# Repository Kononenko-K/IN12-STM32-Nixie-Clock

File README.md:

# IN12-STM32-Nixie-Clock

STM32 Nixie clock project with four Soviet IN-12 indicators.

<br/>

## Overview

<br/>

This project provides a complete solution for building an STM32-powered 
Nixie clock with Soviet IN-12 tubes. It operates on a 5V power supply 
via a Type-C connector and features an internal high voltage generator.

## Hardware

<br/>

### [**Display Module**](/Hardware/nixie%20display/project.pdf)
- Utilizes the K155ID1 (equivalent to SN74141N) as a high-voltage 
BCD-to-decimal decoder.
- Drives four Nixie tubes using dynamic scanning with TLP627 optocouplers.

### [**Controller Module**](/Hardware/mcu%20board/project.pdf)
- Based on the STM32F103C8Tx microcontroller, featuring:
  - Internal RTC peripheral for timekeeping;
  - Battery input for maintaining time during power off;
  - Boost converter for high-voltage generation using a PWM signal from 
one of the MCU's timers;
  - Four WS2812B addressable RGB LEDs for tube illumination.

### **Connection Guide**

| **Display Module** | **Controller Module** |
|--------------------|-----------------------|
| A1                 | PA4                   |
| A2                 | PA6                   |
| A3                 | PB0                   |
| A4                 | PB2                   |
|--------------------|-----------------------|
| D0                 | PA5                   |
| D1                 | PB1                   |
| D2                 | PB10                  |
| D3                 | PA7                   |
|--------------------|-----------------------|
| NE                 | PA10                  |
|--------------------|-----------------------|
| +180V              | HV                    |
|--------------------|-----------------------|
| +5V                | +5V                   |

Connect all respective GNDs together.

## Firmware

The firmware is developed as a Makefile project, generated with 
STM32CubeMX. It can be built using:

```sh
make clean && make
```

To upload the firmware, use ST-LINK/V2 and OpenOCD with the following 
command:

```sh
openocd -f interface/stlink.cfg \
          -f target/stm32f1x.cfg \
          -c "init; reset halt; flash write_image erase ./build/new_nixie.bin 0x08000000; reset halt; exit"
```

The code implements firmware protection and it can be removed with:
```sh
openocd -f interface/stlink.cfg \
          -f target/stm32f1x.cfg \
          -c "init; reset halt; stm32f1x unlock 0; reset halt; exit"
```

For convenience, you can use the provided scripts:
- [flash.sh](/Firmware/flash.sh)
- [remove_protection.sh](/Firmware/remove_protection.sh)

The boost converter's duty cycle may require adjustment based on component 
type. Additionally, delay settings can be fine-tuned for optimal tube 
switching. The firmware includes a feature to prevent cathode poisoning by 
cycling through all tubes every 5 minutes. Also, there are 15 different modes 
of illumination using addressable LEDs.

## License

- The **Firmware** in this project is licensed under the 
[MIT License](/Firmware/LICENSE), with the exception of portions of the 
firmware code that are copyrighted by STMicroelectronics; such portions are 
subject to the original licensing terms provided by STMicroelectronics.
- The **Hardware** in this project is licensed under the 
[CERN Open Hardware Licence Permissive (CERN OHL-P)](/Hardware/LICENSE).

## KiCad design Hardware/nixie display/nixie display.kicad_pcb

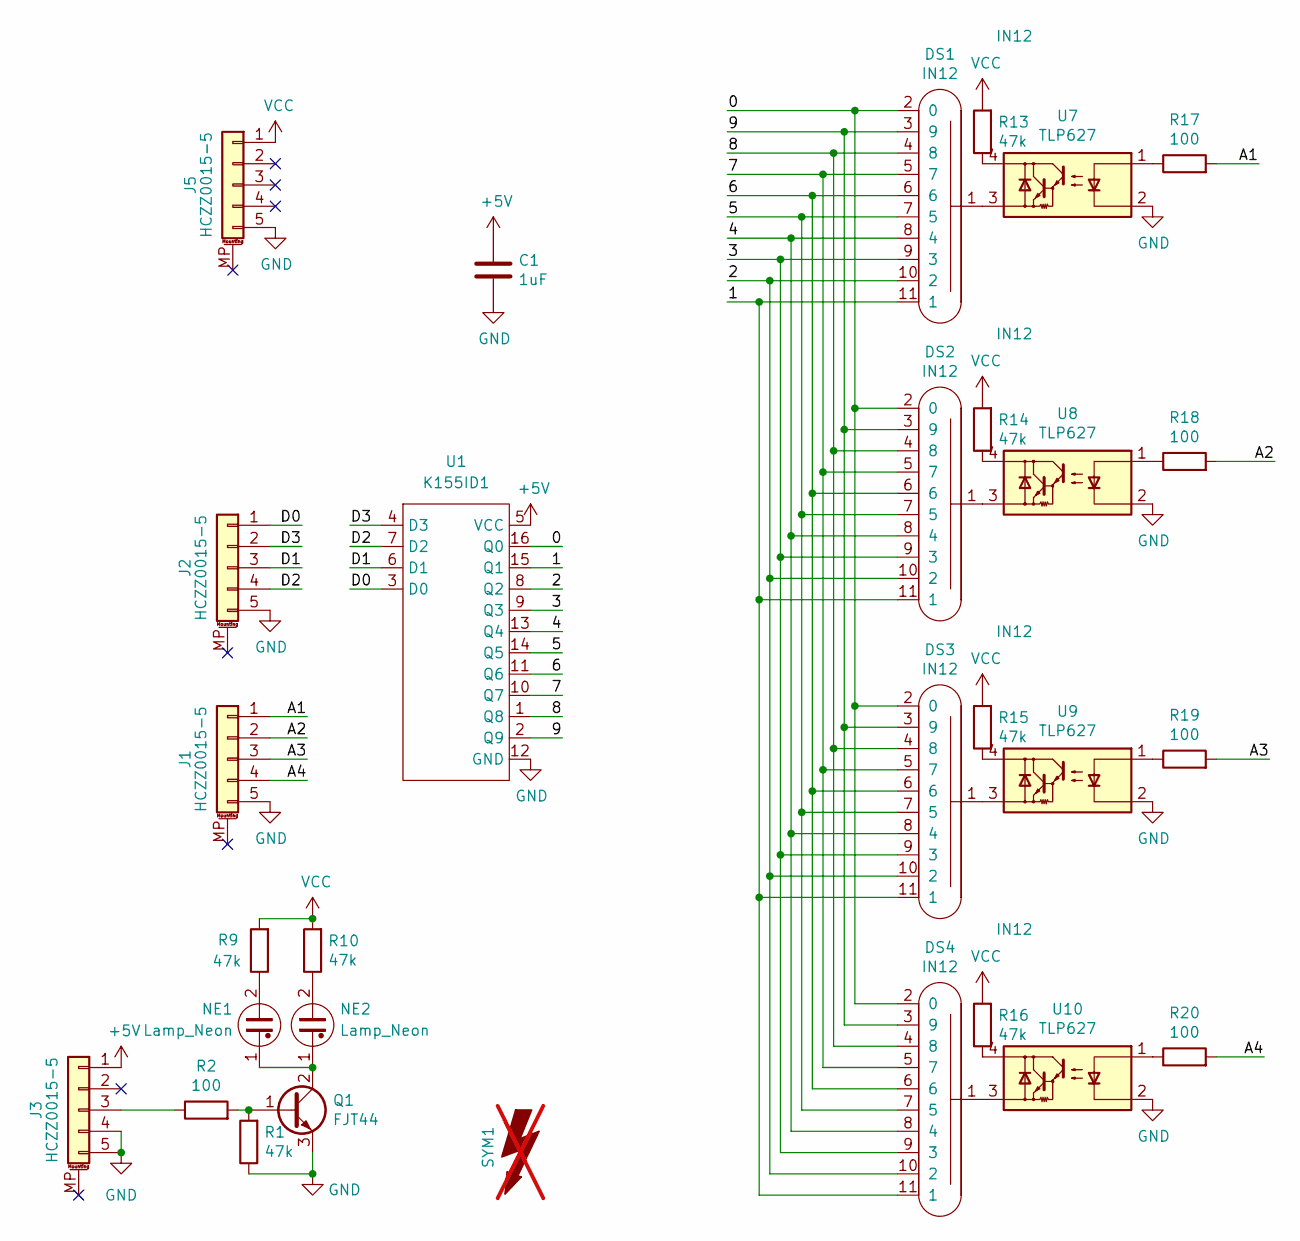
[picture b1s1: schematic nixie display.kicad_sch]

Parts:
C1: 1uF; C_1206_3216Metric_Pad1.42x1.75mm_HandSolder; Part Number CC1206KKX7R9BB105
DS1, DS2, DS3, DS4: IN12; in12; Part Number IN12
J1, J2, J3, J5: HCZZ0015-5; Molex_PicoBlade_53398-0571_1x05-1MP_P1.25mm_Vertical; Part Number HCZZ0015-5
NE1, NE2: Lamp_Neon; neon; Part Number NE-2
Q1: FJT44; SOT-223-3_TabPin2; Part Number FJT44
R1: 47k; R_1206_3216Metric_Pad1.30x1.75mm_HandSolder; Part Number RC1206JR-0747KL
R2: 100; R_1206_3216Metric_Pad1.30x1.75mm_HandSolder; Part Number RC1206JR-07100RL
R9, R10, R13, R14, R15, R16: 47k; R_1206_3216Metric_Pad1.42x1.75mm_HandSolder; Part Number RC1206JR-0747KL
R17, R18, R19, R20: 100; R_1206_3216Metric_Pad1.42x1.75mm_HandSolder; Part Number RC1206JR-07100RL
SYM1: SYM_Flash_Large; HighVoltage; not fitted
U1: DS1009-16AT1NX-0A2; DIP-16_W7.62mm_Socket; Part Number DS1009-16AT1NX-0A2
U7, U8, U9, U10: TLP627; SMDIP-4_W7.62mm; Part Number TLP627(TP1,F)

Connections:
+5V: C1.1, J3.1, U1.5 (VCC)
/0: DS1.2 (0), DS2.2 (0), DS3.2 (0), DS4.2 (0), U1.16 (Q0)
/1: DS1.11 (1), DS2.11 (1), DS3.11 (1), DS4.11 (1), U1.15 (Q1)
/2: DS1.10 (2), DS2.10 (2), DS3.10 (2), DS4.10 (2), U1.8 (Q2)
/3: DS1.9 (3), DS2.9 (3), DS3.9 (3), DS4.9 (3), U1.9 (Q3)
/4: DS1.8 (4), DS2.8 (4), DS3.8 (4), DS4.8 (4), U1.13 (Q4)
/5: DS1.7 (5), DS2.7 (5), DS3.7 (5), DS4.7 (5), U1.14 (Q5)
/6: DS1.6, DS2.6, DS3.6, DS4.6, U1.11 (Q6)
/7: DS1.5 (7), DS2.5 (7), DS3.5 (7), DS4.5 (7), U1.10 (Q7)
/8: DS1.4 (8), DS2.4 (8), DS3.4 (8), DS4.4 (8), U1.1 (Q8)
/9: DS1.3 (9), DS2.3 (9), DS3.3 (9), DS4.3 (9), U1.2 (Q9)
/A1: J1.1, R17.2
/A2: J1.2, R18.2
/A3: J1.3, R19.2
/A4: J1.4, R20.2
/D0: J2.1, U1.3 (D0)
/D1: J2.3, U1.6 (D1)
/D2: J2.4, U1.7 (D2)
/D3: J2.2, U1.4 (D3)
GND: C1.2, J1.5, J2.5, J3.4, J3.5, J5.5, Q1.3 (E), R1.1, U1.12 (GND), U7.2, U8.2, U9.2, U10.2
unnamed: DS1.1, U7.3
unnamed: DS2.1, U8.3
unnamed: DS3.1, U9.3
unnamed: DS4.1, U10.3
unnamed: J3.3, R2.1
unnamed: NE1.2, R9.1
unnamed: NE2.2, R10.1
unnamed: Q1.1 (B), R1.2, R2.2
unnamed: NE1.1, NE2.1, Q1.2 (C)
unnamed: R13.1, U7.4
unnamed: R14.1, U8.4
unnamed: R15.1, U9.4
unnamed: R16.1, U10.4
unnamed: R17.1, U7.1
unnamed: R18.1, U8.1
unnamed: R19.1, U9.1
unnamed: R20.1, U10.1
VCC: J5.1, R9.2, R10.2, R13.2, R14.2, R15.2, R16.2

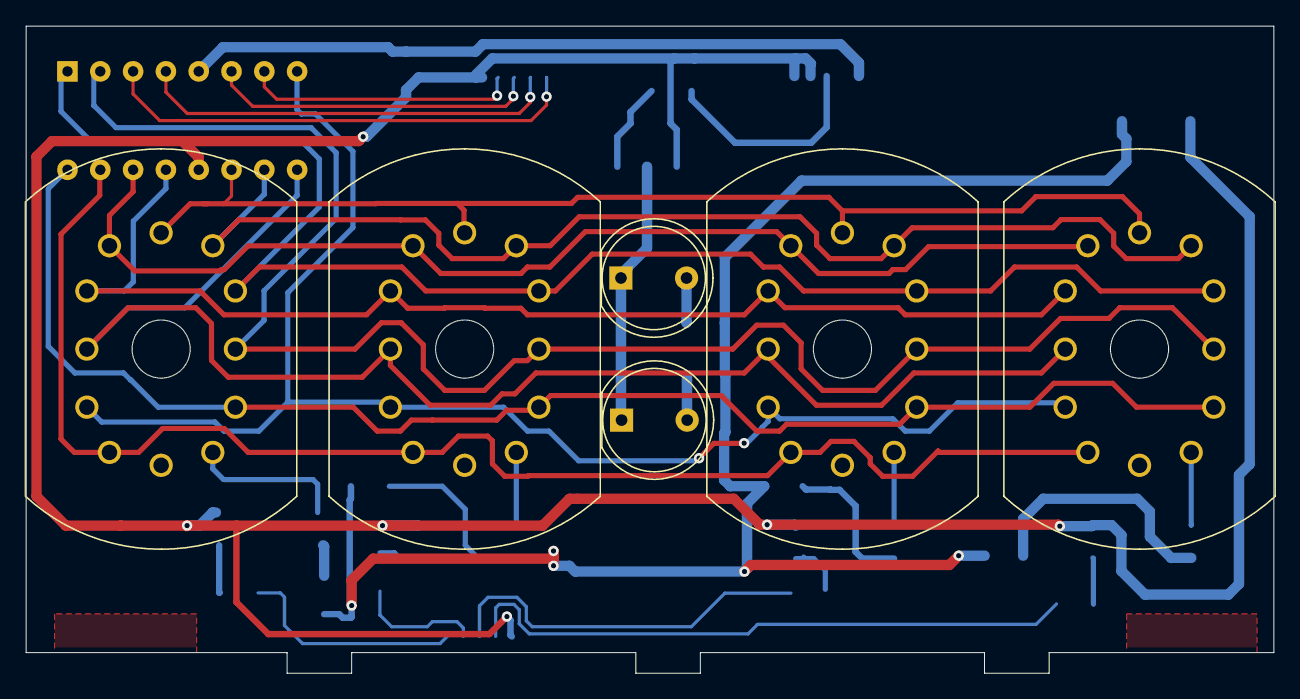
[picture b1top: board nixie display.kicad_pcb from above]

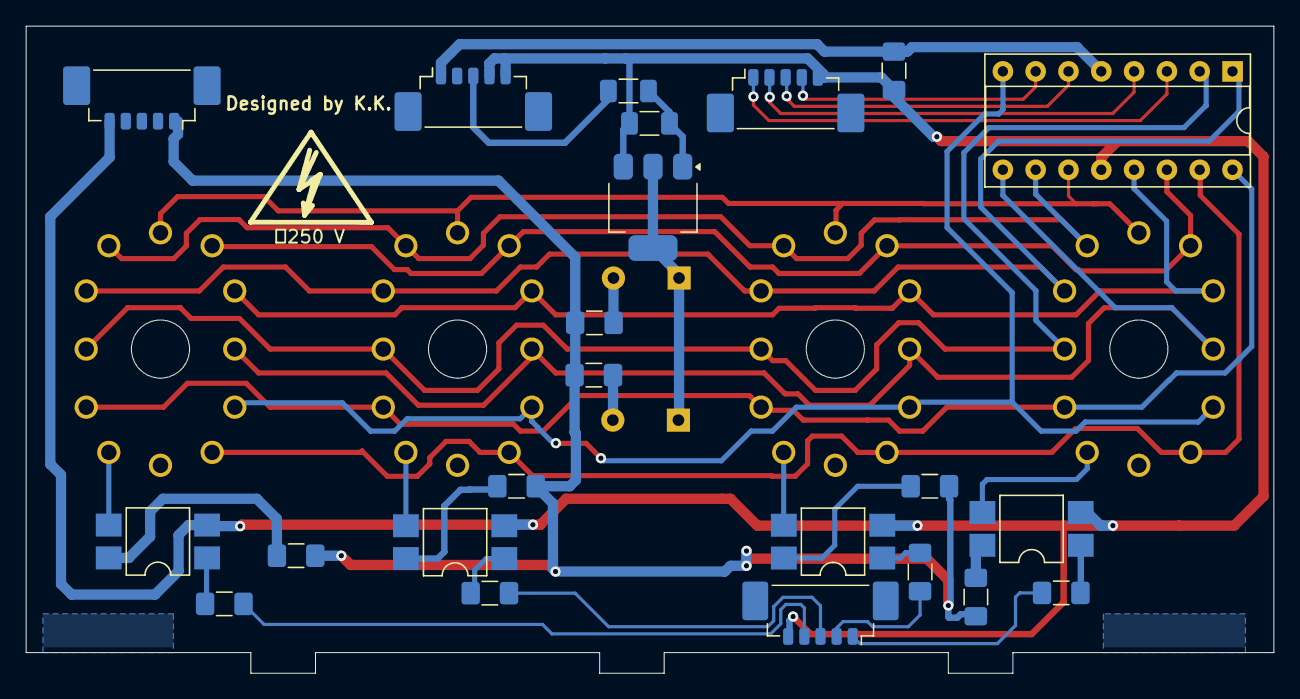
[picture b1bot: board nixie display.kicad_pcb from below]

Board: 2 copper layers, 96.6 x 50.1 mm, 30 parts (24 on the bottom side), 38 nets.

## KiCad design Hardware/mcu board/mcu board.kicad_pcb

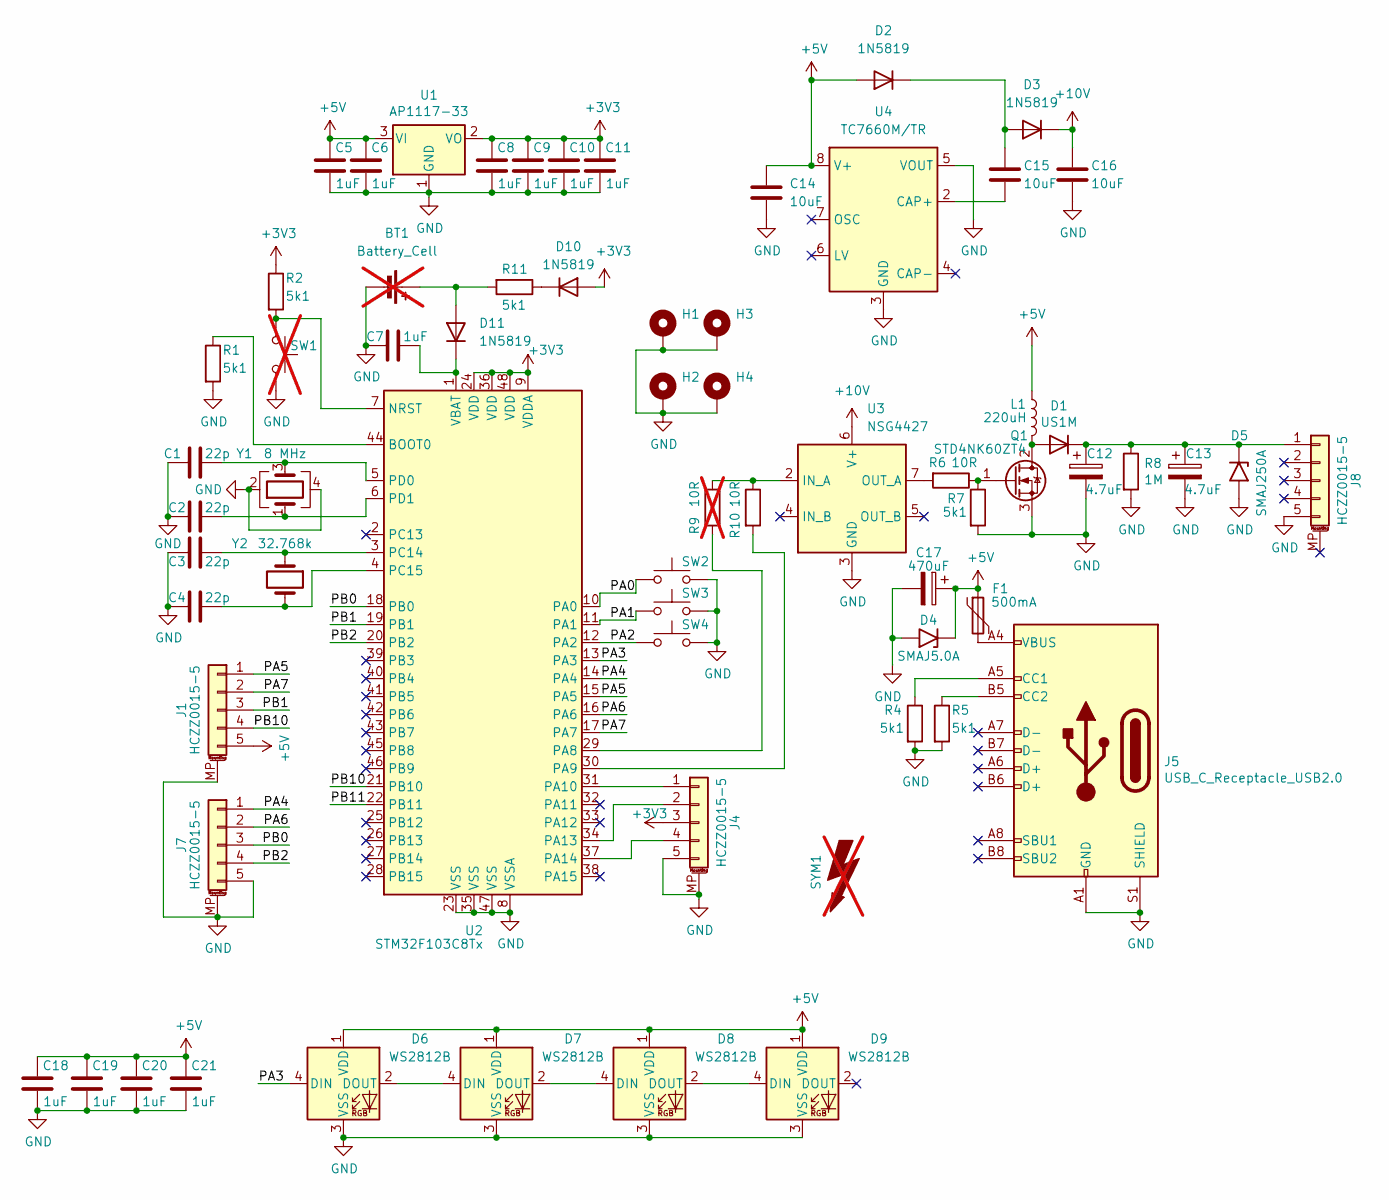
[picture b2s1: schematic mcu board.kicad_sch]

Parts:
BT1: Battery_Cell; BatteryHolder_Seiko_MS621F; not fitted
C1, C2, C3, C4: 22p; C_0402_1005Metric_Pad0.74x0.62mm_HandSolder; Part Number CC0402JRNPO9BN180
C5, C6, C7, C8, C9, C10, C11, C18, C19, C20, C21: CGA0603X5R105K160JT; C_0603_1608Metric_Pad1.08x0.95mm_HandSolder; Part Number CC0603KRX5R8BB105
C12, C13: 189RV165; CP_Elec_8x10; Part Number 189RV165
C14, C15, C16: 10uF; C_1206_3216Metric_Pad1.33x1.80mm_HandSolder; Part Number CC1206KKX5R8BB106
C17: GVE1C477M0810CNVC; CP_Elec_8x10; Part Number GVE1C477M0810CNVC
D1: US1M; D_SMA; Part Number US1M
D2, D3, D10, D11: 1N5819; D_SOD-123; Part Number 1N5819HW-7-F
D4: SMAJ5.0A; D_SMA; Part Number SMAJ5.0A
D5: SMAJ250A; D_SMA; Part Number SMAJ250A
D6, D7, D8, D9: WS2812B; LED_WS2812B_PLCC4_5.0x5.0mm_P3.2mm; Part Number XL-5050RGBC-WS2812B
F1: JK-MSMD050-30; Fuse_1812_4532Metric_Pad1.30x3.40mm_HandSolder; Part Number JK-MSMD050-30
H1, H2, H3, H4: SMTSO3080MTJ; Mounting_Wuerth_WA-SMSI-M3_H8mm_9774080360; Part Number SMTSO3080MTJ
J1, J4, J7, J8: HCZZ0015-5; Molex_PicoBlade_53398-0571_1x05-1MP_P1.25mm_Vertical; Part Number HCZZ0015-5
J5: USB_C_Receptacle_USB2.0; USB_C_Receptacle_Palconn_UTC16-G; Part Number TYPE-C-31-M-12
L1: CYH127-220UH; L_Wuerth_WE-PD-Typ-LS_Handsoldering; Part Number SHOU HAN CYH125-330UH
Q1: STD4NK60ZT4; TO-252-2; Part Number STD4NK60ZT4
R1, R2, R4, R5, R7, R11: 5k1; R_0402_1005Metric_Pad0.72x0.64mm_HandSolder; Part Number RC0402FR-075K1L
R6, R10: 10R; R_0402_1005Metric_Pad0.72x0.64mm_HandSolder; Part Number RC0402FR-0710RL
R8: 1M; R_1206_3216Metric_Pad1.30x1.75mm_HandSolder; Part Number RC1206FR-071ML
R9: 10R; R_0402_1005Metric_Pad0.72x0.64mm_HandSolder; not fitted
SW1: TS-1101-C-W; SW_SPST_CK_RS282G05A3; not fitted
SW2, SW3, SW4: XKB5858-W-F-75; Part Number XKB5858-W-F-75
SYM1: SYM_Flash_Large; HighVoltage; not fitted
U1: AP1117-33; SOT-223-3_TabPin2; Part Number AMS1117-3.3
U2: STM32F103C8Tx; LQFP-48_7x7mm_P0.5mm; Part Number STM32F103C8T6
U3: NSG4427; SOIC-8_3.9x4.9mm_P1.27mm; Part Number NSG4427
U4: TC7660M/TR; SOIC-8_3.9x4.9mm_P1.27mm; Part Number TC7660M/TR
Y1: TAXM8M4RFDCET2T; Crystal_SMD_3225-4Pin_3.2x2.5mm; Part Number TAXM8M4RFDCET2T
Y2: XKXGI-SUA-32.768K; Crystal_SMD_G8-2Pin_3.2x1.5mm_HandSoldering; Part Number XKXGI-SUA-32.768K

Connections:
+3V3: C8.2, C9.2, C10.2, C11.2, D10.2 (A), J4.3, R2.1, U1.2 (VO), U2.9 (VDDA), U2.24 (VDD), U2.36 (VDD), U2.48 (VDD)
+5V: C5.2, C6.2, C14.1, C17.1, C18.2, C19.2, C20.2, C21.2, D2.2 (A), D4.1 (A1), D6.1 (VDD), D7.1 (VDD), D8.1 (VDD), D9.1 (VDD), F1.1, J1.5, L1.1, U1.3 (VI), U4.8 (V+)
+10V: C16.1, D3.1 (K), U3.6 (V+)
/PA0: SW2.1, U2.10 (PA0)
/PA1: SW3.1, U2.11 (PA1)
/PA2: SW4.1, U2.12 (PA2)
/PA3: D6.4 (DIN), U2.13 (PA3)
/PA4: J7.1, U2.14 (PA4)
/PA5: J1.1, U2.15 (PA5)
/PA6: J7.2, U2.16 (PA6)
/PA7: J1.2, U2.17 (PA7)
/PB0: J7.3, U2.18 (PB0)
/PB1: J1.3, U2.19 (PB1)
/PB2: J7.4, U2.20 (PB2)
/PB10: J1.4, U2.21 (PB10)
/PB11: U2.22 (PB11)
GND: BT1.2 (-), C1.2, C2.2, C3.2, C4.2, C5.1, C6.1, C7.1, C8.1, C9.1, C10.1, C11.1, C12.2, C13.2, C14.2, C16.2, C17.2, C18.1, C19.1, C20.1, C21.1, D4.2 (A2), D5.2 (A2), D6.3 (VSS), D7.3 (VSS), D8.3 (VSS), D9.3 (VSS), H1.1, H2.1, H3.1, H4.1, J1.MP (MountPin), J4.5, J4.MP (MountPin), J5.A1 (GND), J5.A12 (GND), J5.B1 (GND), J5.B12 (GND), J5.S1 (SHIELD), J7.5, J7.MP (MountPin), J8.5, Q1.3 (S), R1.2, R4.2, R5.2, R7.2, R8.2, SW1.2, SW2.2, SW3.2, SW4.2, U1.1 (GND), U2.8 (VSSA), U2.23 (VSS), U2.35 (VSS), U2.47 (VSS), U3.3 (GND), U4.3 (GND), U4.5 (VOUT), Y1.2, Y1.4
unnamed: BT1.1 (+), D11.2 (A), R11.2
unnamed: D1.2 (A), L1.2, Q1.2 (D)
unnamed: C12.1, C13.1, D1.1 (K), D5.1 (A1), J8.1, R8.1
unnamed: C15.1, D2.1 (K), D3.2 (A)
unnamed: D6.2 (DOUT), D7.4 (DIN)
unnamed: D7.2 (DOUT), D8.4 (DIN)
unnamed: D8.2 (DOUT), D9.4 (DIN)
unnamed: D10.1 (K), R11.1
unnamed: C7.2, D11.1 (K), U2.1 (VBAT)
unnamed: F1.2, J5.A4 (VBUS), J5.A9 (VBUS), J5.B4 (VBUS), J5.B9 (VBUS)
unnamed: J4.1, U2.31 (PA10)
unnamed: J4.2, U2.34 (PA13)
unnamed: J4.4, U2.37 (PA14)
unnamed: J5.A5 (CC1), R4.1
unnamed: J5.B5 (CC2), R5.1
unnamed: Q1.1 (G), R6.1, R7.1
unnamed: R1.1, U2.44 (BOOT0)
unnamed: R2.2, SW1.1, U2.7 (NRST)
unnamed: R9.2, U2.29 (PA8)
unnamed: R10.2, U2.30 (PA9)
unnamed: C3.1, U2.3 (PC14), Y2.1
unnamed: C4.1, U2.4 (PC15), Y2.2
unnamed: C1.1, U2.5 (PD0), Y1.3
unnamed: C2.1, U2.6 (PD1), Y1.1
unnamed: R9.1, R10.1, U3.2 (IN_A)
unnamed: R6.2, U3.7 (OUT_A)
unnamed: C15.2, U4.2 (CAP+)

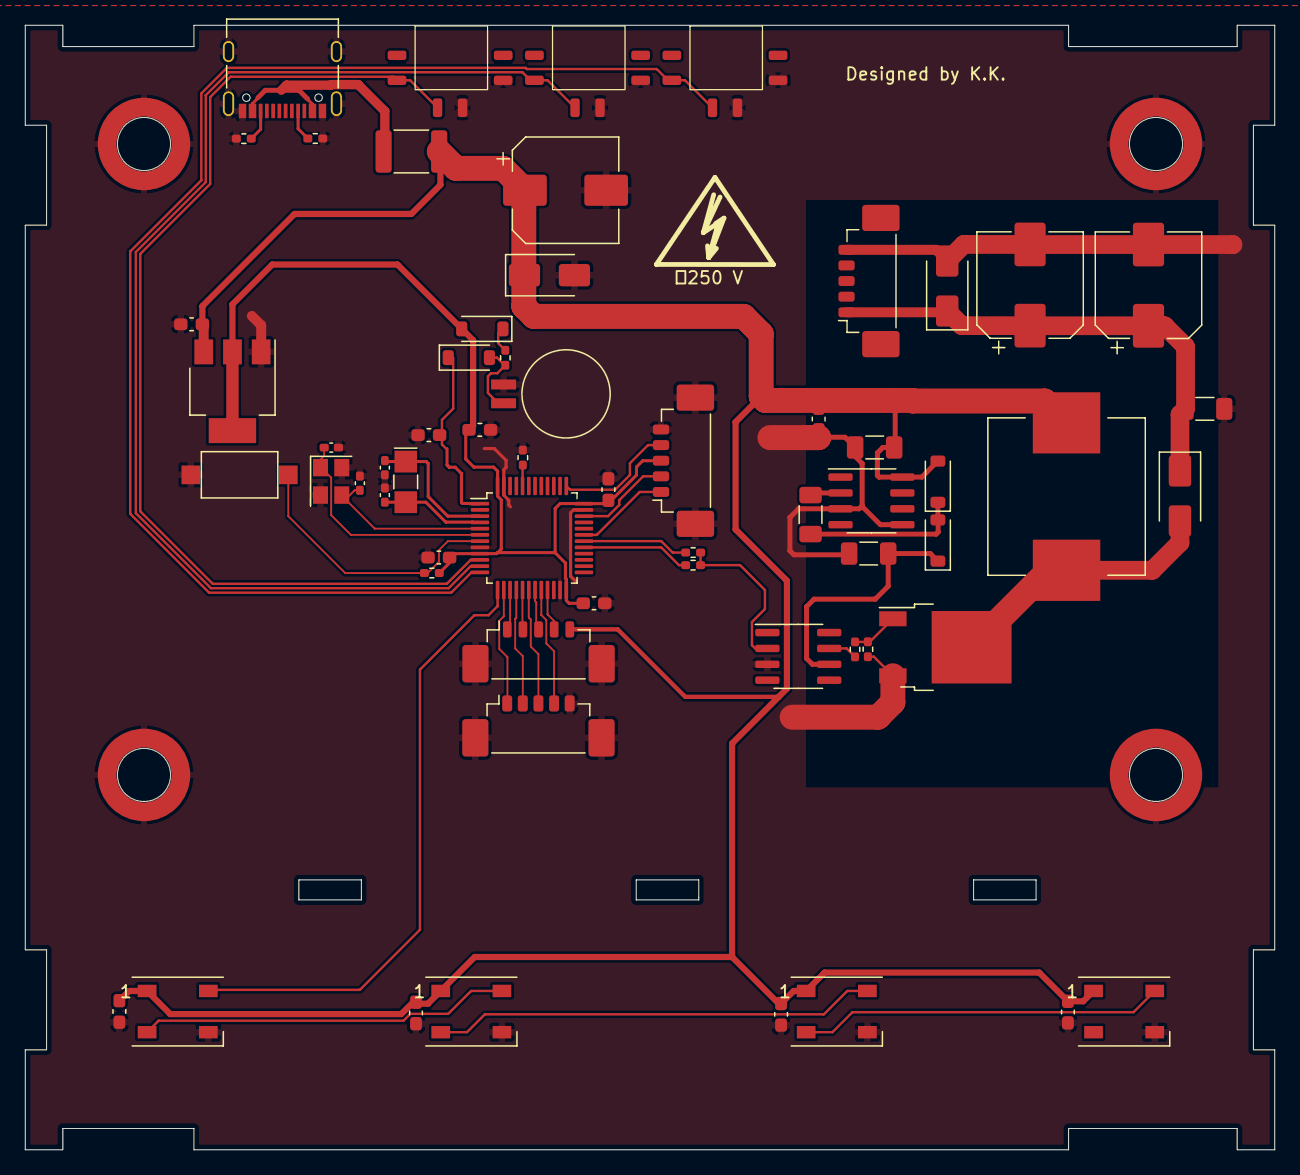
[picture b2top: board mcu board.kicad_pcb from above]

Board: 2 copper layers, 100.0 x 90.0 mm, 66 parts (0 on the bottom side), 43 nets.

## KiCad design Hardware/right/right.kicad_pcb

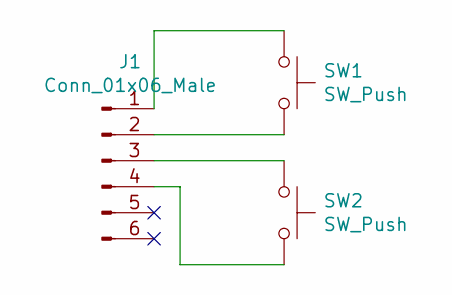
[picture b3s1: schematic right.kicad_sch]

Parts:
J1: Conn_01x06_Male; PinHeader_2x03_P2.54mm_Vertical_SMD
SW1, SW2: SW_Push; SW_Push_1P1T_NO_6x6mm_H9.5mm

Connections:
unnamed: J1.1, SW1.1
unnamed: J1.2, SW1.2
unnamed: J1.3, SW2.1
unnamed: J1.4, SW2.2

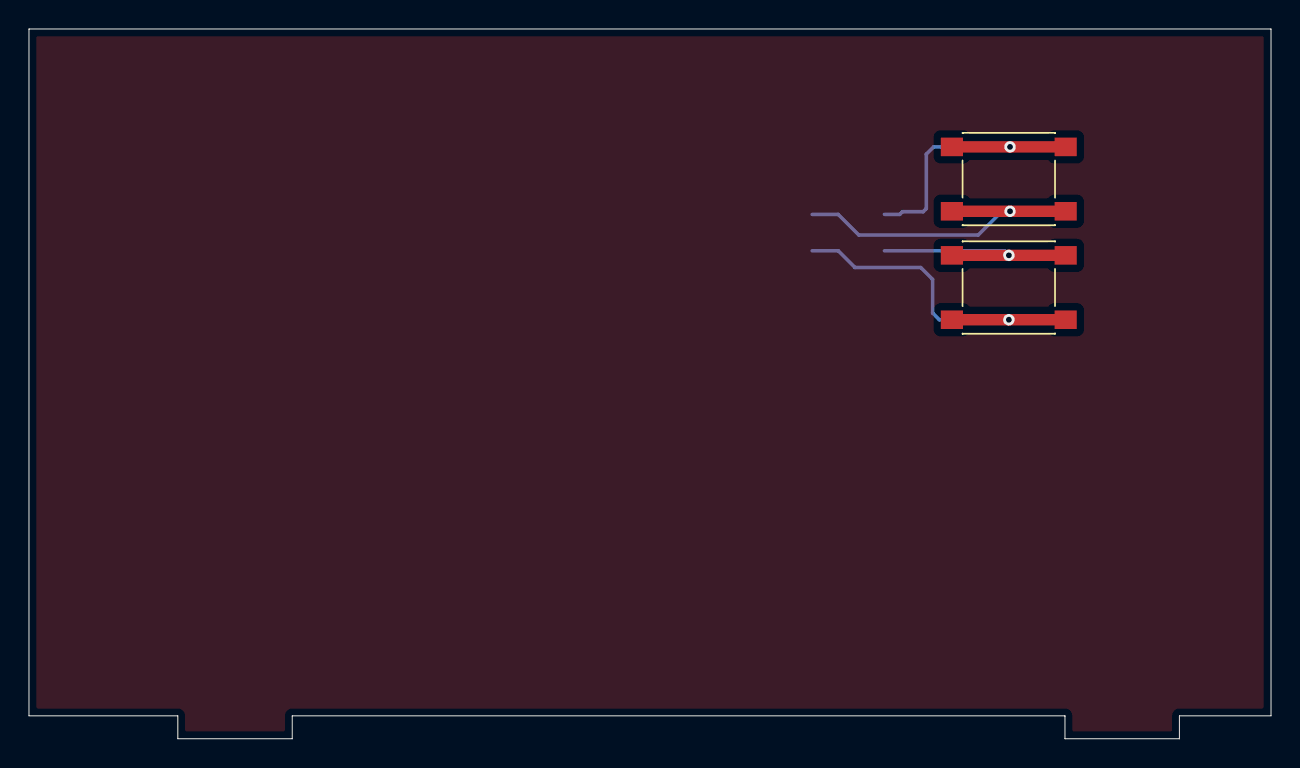
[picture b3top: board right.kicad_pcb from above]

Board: 2 copper layers, 86.8 x 49.6 mm, 3 parts (1 on the bottom side), 4 nets.

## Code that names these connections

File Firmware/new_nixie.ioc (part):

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Mcu.Name=STM32F103C(8-B)Tx
Mcu.Package=LQFP48
Mcu.UserName=STM32F103C8Tx
PA0-WKUP.GPIOParameters=GPIO_PuPd
PA0-WKUP.GPIO_PuPd=GPIO_PULLUP
PA0-WKUP.Signal=GPIO_Input
PA1.GPIOParameters=GPIO_PuPd
PA1.GPIO_PuPd=GPIO_PULLUP
PA1.Signal=GPIO_Input
PA10.Signal=S_TIM1_CH3
PA13.Mode=Serial_Wire
PA13.Signal=SYS_JTMS-SWDIO
PA14.Mode=Serial_Wire
PA14.Signal=SYS_JTCK-SWCLK
PA2.GPIOParameters=GPIO_PuPd
PA2.GPIO_PuPd=GPIO_PULLUP
PA2.Signal=GPIO_Input
PA3.GPIOParameters=GPIO_Speed
PA3.GPIO_Speed=GPIO_SPEED_FREQ_HIGH
PA3.Signal=GPIO_Output
PA4.Signal=GPIO_Output
PA5.Signal=GPIO_Output
PA6.Signal=GPIO_Output
PA7.Signal=GPIO_Output
PA9.Signal=S_TIM1_CH2
PB0.Signal=GPIO_Output
PB1.Signal=GPIO_Output
PB10.Signal=GPIO_Output
PB2.Signal=GPIO_Output
PC14-OSC32_IN.Mode=LSE-External-Oscillator
PC14-OSC32_IN.Signal=RCC_OSC32_IN
PC15-OSC32_OUT.Mode=LSE-External-Oscillator
PC15-OSC32_OUT.Signal=RCC_OSC32_OUT
PD0-OSC_IN.Mode=HSE-External-Oscillator
PD0-OSC_IN.Signal=RCC_OSC_IN
PD1-OSC_OUT.Mode=HSE-External-Oscillator
PD1-OSC_OUT.Signal=RCC_OSC_OUT
RCC.SYSCLKFreq_VALUE=72000000
RCC.SYSCLKSource=RCC_SYSCLKSOURCE_PLLCLK
board=custom

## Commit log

2025-07-04 Added license information
2025-07-04 Minor fix in README
2025-07-31 Major HW and FW improvements
2025-07-31 README fixed
